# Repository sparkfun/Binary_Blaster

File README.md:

Binary Blaster Kit
==============

[Binary Blaster (KIT-12037)](https://www.sparkfun.com/products/12037)

This beginner's thru-hole soldering kit is a fun way to learn binary conversion. It displays a decimal value, 
and you are challenged to press the buttons to represent the correct binary version. Correctly press all 15 
values and you win!

Repository Contents
-------------------

* **/Firmware** - Firmware that comes programmed on the kit.
* **/Hardware** - All Eagle design files (.brd, .sch)

Documentation
-------------------
* [Assembly Guide](https://learn.sparkfun.com/tutorials/binary-blaster-assembly-guide)

License Information
-------------------
The hardware is released under [Creative Commons ShareAlike 4.0 International](https://creativecommons.org/licenses/by-sa/4.0/).
The code is beerware; if you see me (or any other SparkFun employee) at the local, and you've found our code helpful, please buy us a round!

Distributed as-is; no warranty is given.

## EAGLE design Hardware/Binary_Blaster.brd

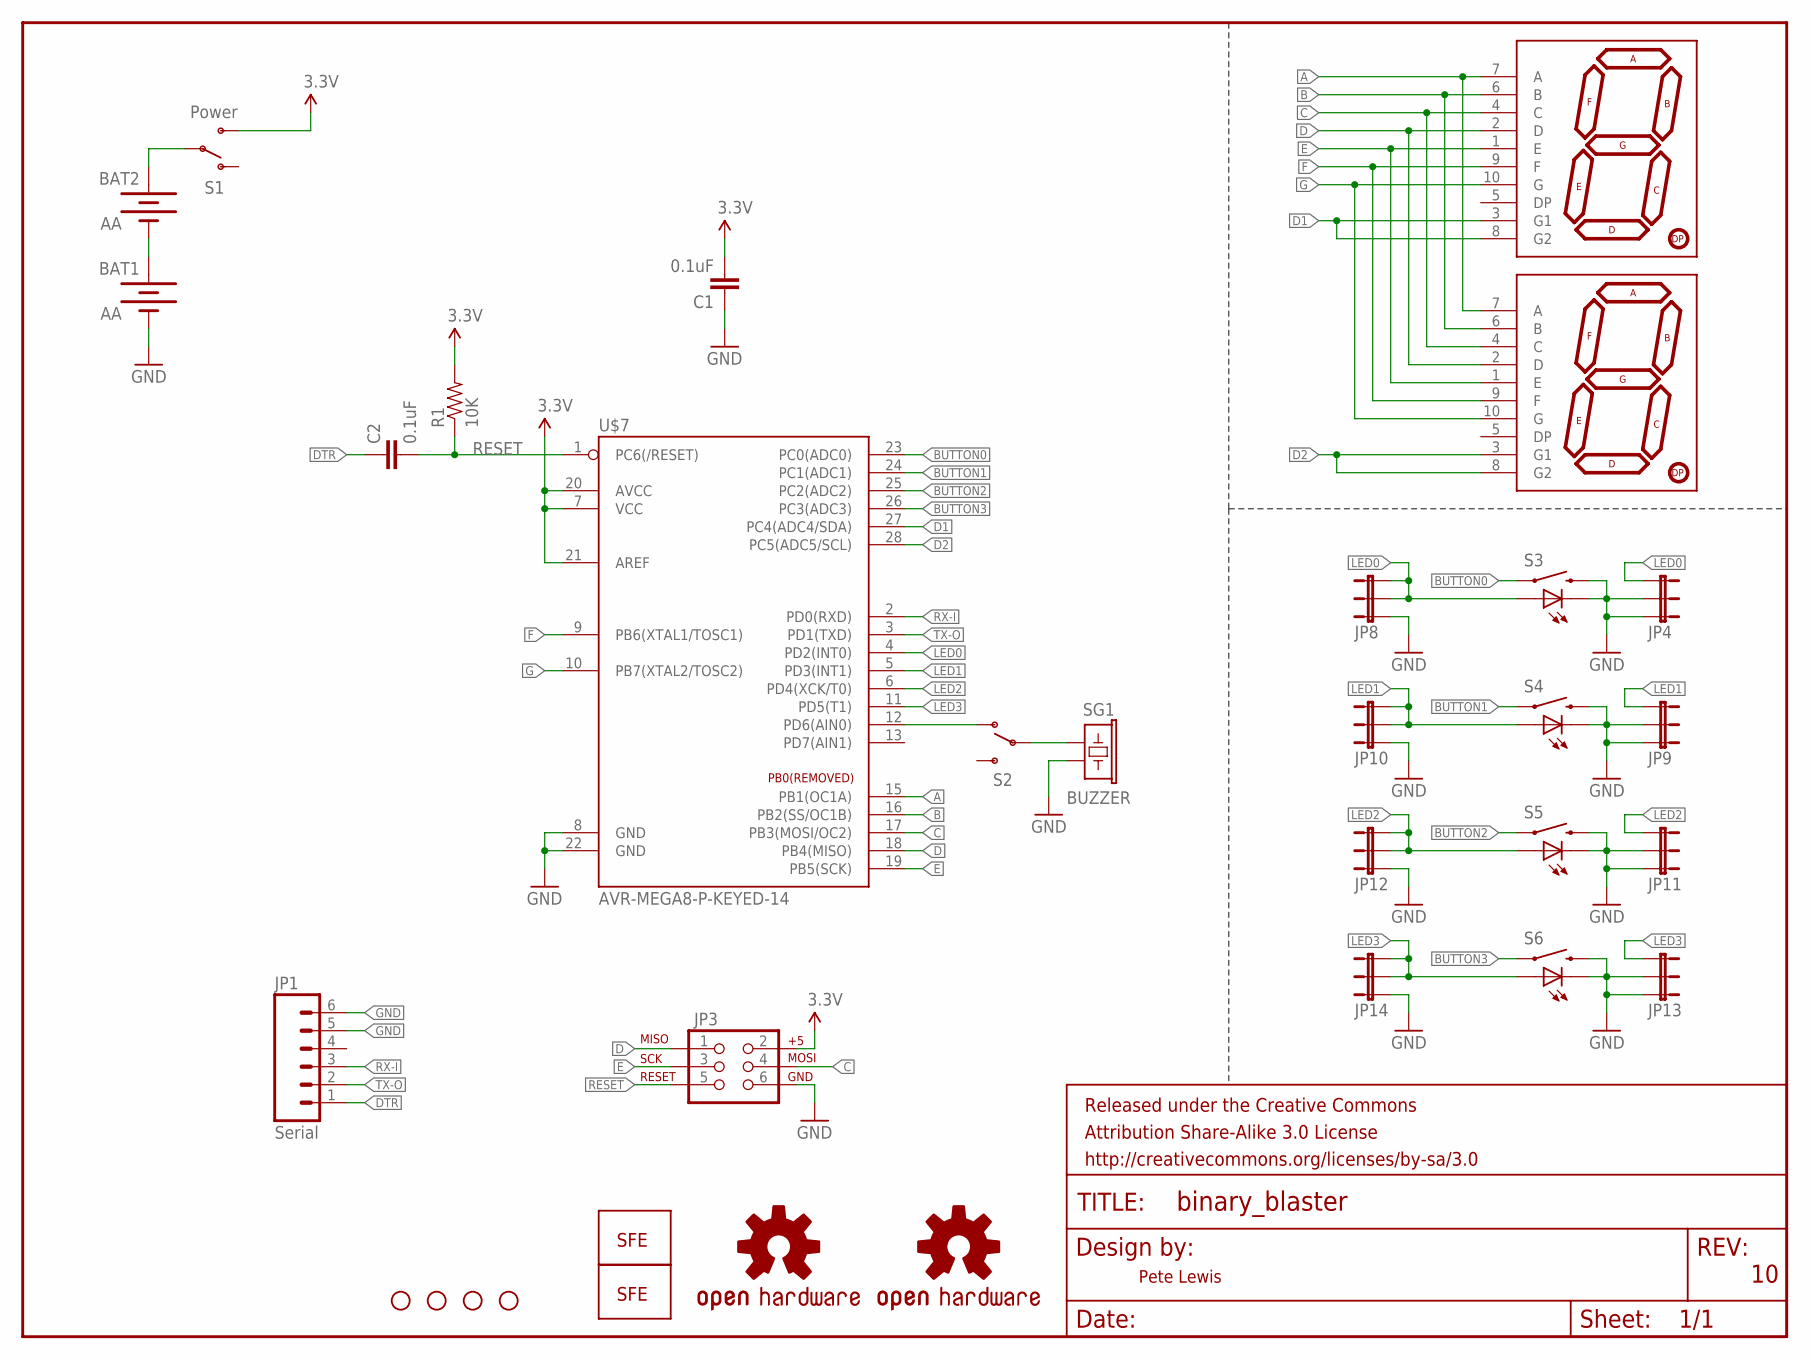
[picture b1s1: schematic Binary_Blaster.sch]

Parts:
BAT1, BAT2: AA; BATTERY-AA-KIT
C1, C2: 0.1uF; CAP-PTH-SMALL-KIT
FRAME1: FRAME-LETTER; CREATIVE_COMMONS
JP1: Serial; 1X06-NOSILK
JP2, JP5, JP6, JP7: STAND-OFF
JP3: AVR_SPI_PRG_6NS; 2X3-NS
JP4, JP8, JP9, JP10, JP11, JP12, JP13, JP14: JUMPER-3SMD; SJ_3
LOGO1, LOGO2: LOGO-SFENEW; SFE-NEW-WEBLOGO
R1: 10K; AXIAL-0.3-KIT
S1: Power; SWITCH-SPDT_KIT
S2: SWITCH-SPDTKIT; SWITCH-SPDT_KIT
S3, S4, S5, S6: SWITCH-MOMENTARY-LEDEZ; TACTILE-PTH-LED-12MM-EZ
SG1: BUZZER; BUZZER-12MM-KIT
U$1, U$6: 7-SEGMENT-DISPLAY-1"-REDEZ; 7-SEGMENT-1"PTH-EZ
U$2: OSHW-LOGOL; OSHW-LOGO-L
U$3: OSHW-LOGOS; OSHW-LOGO-S
U$7: AVR-MEGA8-P-KEYED-14; DIL28-3_KEYED-14

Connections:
3.3V: C1.2, JP3.2, R1.P$2 (2), S1.3 (S), U$7.7 (VCC), U$7.20 (AVCC), U$7.21 (AREF)
A: U$1.7 (A), U$6.7 (A), U$7.15 (PB1(OC1A))
B: U$1.6 (B), U$6.6 (B), U$7.16 (PB2(SS/OC1B))
BUTTON0: S3.4 (1), U$7.23 (PC0(ADC0))
BUTTON1: S4.4 (1), U$7.24 (PC1(ADC1))
BUTTON2: S5.4 (1), U$7.25 (PC2(ADC2))
BUTTON3: S6.4 (1), U$7.26 (PC3(ADC3))
C: JP3.4, U$1.4 (C), U$6.4 (C), U$7.17 (PB3(MOSI/OC2))
D: JP3.1, U$1.2 (D), U$6.2 (D), U$7.18 (PB4(MISO))
D1: U$1.3 (G1), U$1.8 (G2), U$7.27 (PC4(ADC4/SDA))
D2: U$6.3 (G1), U$6.8 (G2), U$7.28 (PC5(ADC5/SCL))
DTR: C2.1, JP1.1
E: JP3.3, U$1.1 (E), U$6.1 (E), U$7.19 (PB5(SCK))
F: U$1.9 (F), U$6.9 (F), U$7.9 (PB6(XTAL1/TOSC1))
G: U$1.10 (G), U$6.10 (G), U$7.10 (PB7(XTAL2/TOSC2))
GND: BAT1.GND@1 (-), C1.1, JP1.5, JP1.6, JP3.6, JP4.2, JP4.3, JP8.1, JP9.2, JP9.3, JP10.1, JP11.2, JP11.3, JP12.1, JP13.2, JP13.3, JP14.1, S3.2, S3.C, S4.2, S4.C, S5.2, S5.C, S6.2, S6.C, SG1.- (2), U$7.8 (GND), U$7.22 (GND)
LED0: JP4.1, JP8.2, JP8.3, S3.A, U$7.4 (PD2(INT0))
LED1: JP9.1, JP10.2, JP10.3, S4.A, U$7.5 (PD3(INT1))
LED2: JP11.1, JP12.2, JP12.3, S5.A, U$7.6 (PD4(XCK/T0))
LED3: JP13.1, JP14.2, JP14.3, S6.A, U$7.11 (PD5(T1))
unnamed: S2.2, SG1.+ (1)
unnamed: BAT2.PWR@1 (+), S1.2
unnamed: S2.1 (O), U$7.12 (PD6(AIN0))
unnamed: BAT1.PWR@1 (+), BAT2.GND@1 (-)
RESET: C2.2, JP3.5, R1.P$1 (1), U$7.1 (PC6(/RESET))
RX-I: JP1.3, U$7.2 (PD0(RXD))
TX-O: JP1.2, U$7.3 (PD1(TXD))

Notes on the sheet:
Pete Lewis

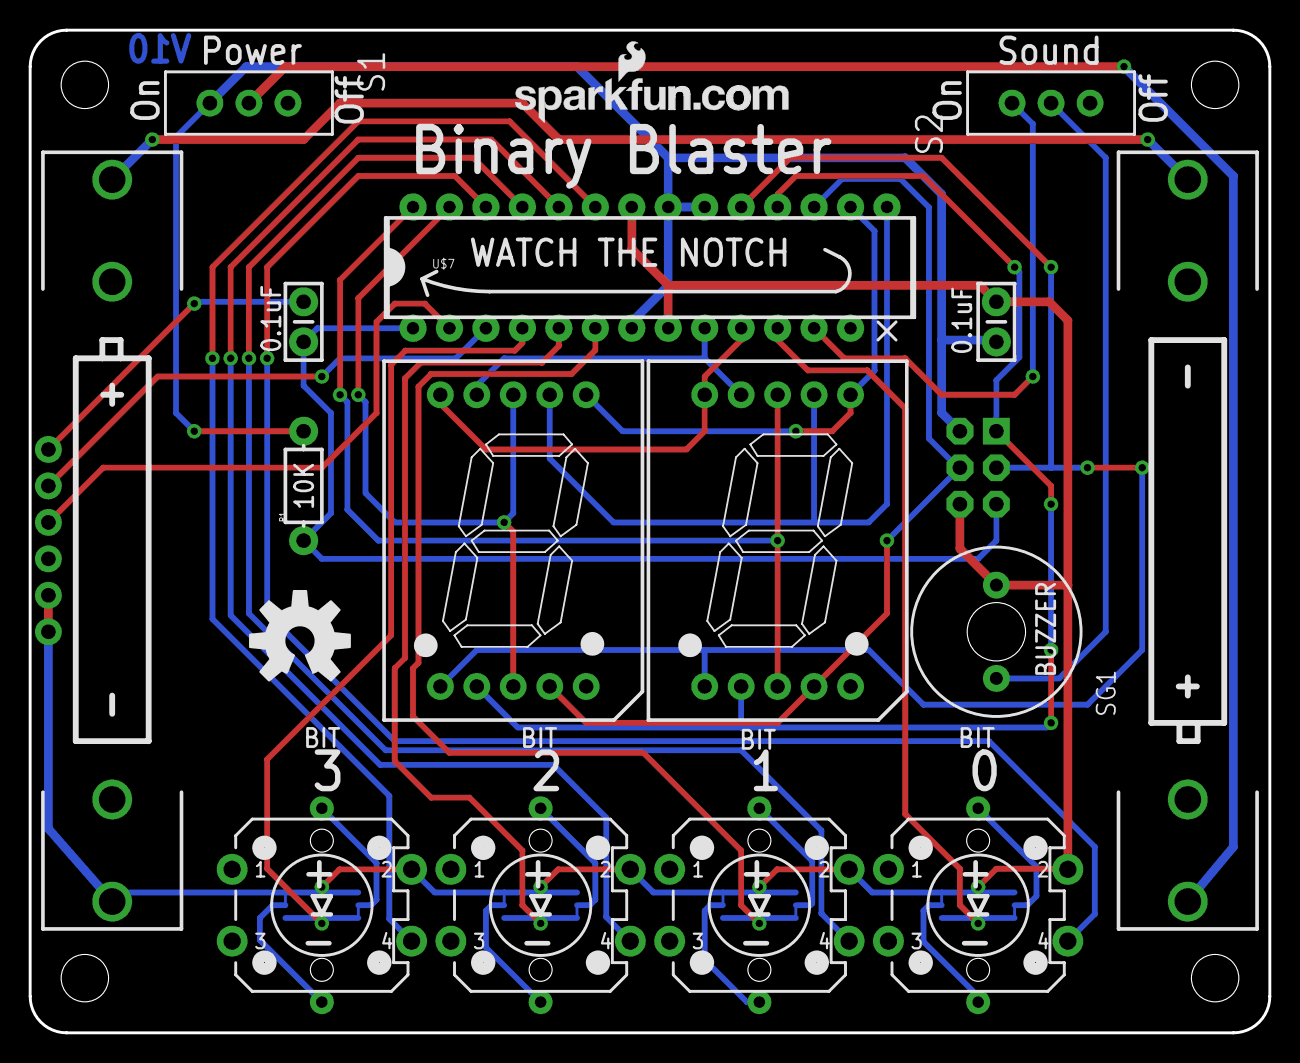
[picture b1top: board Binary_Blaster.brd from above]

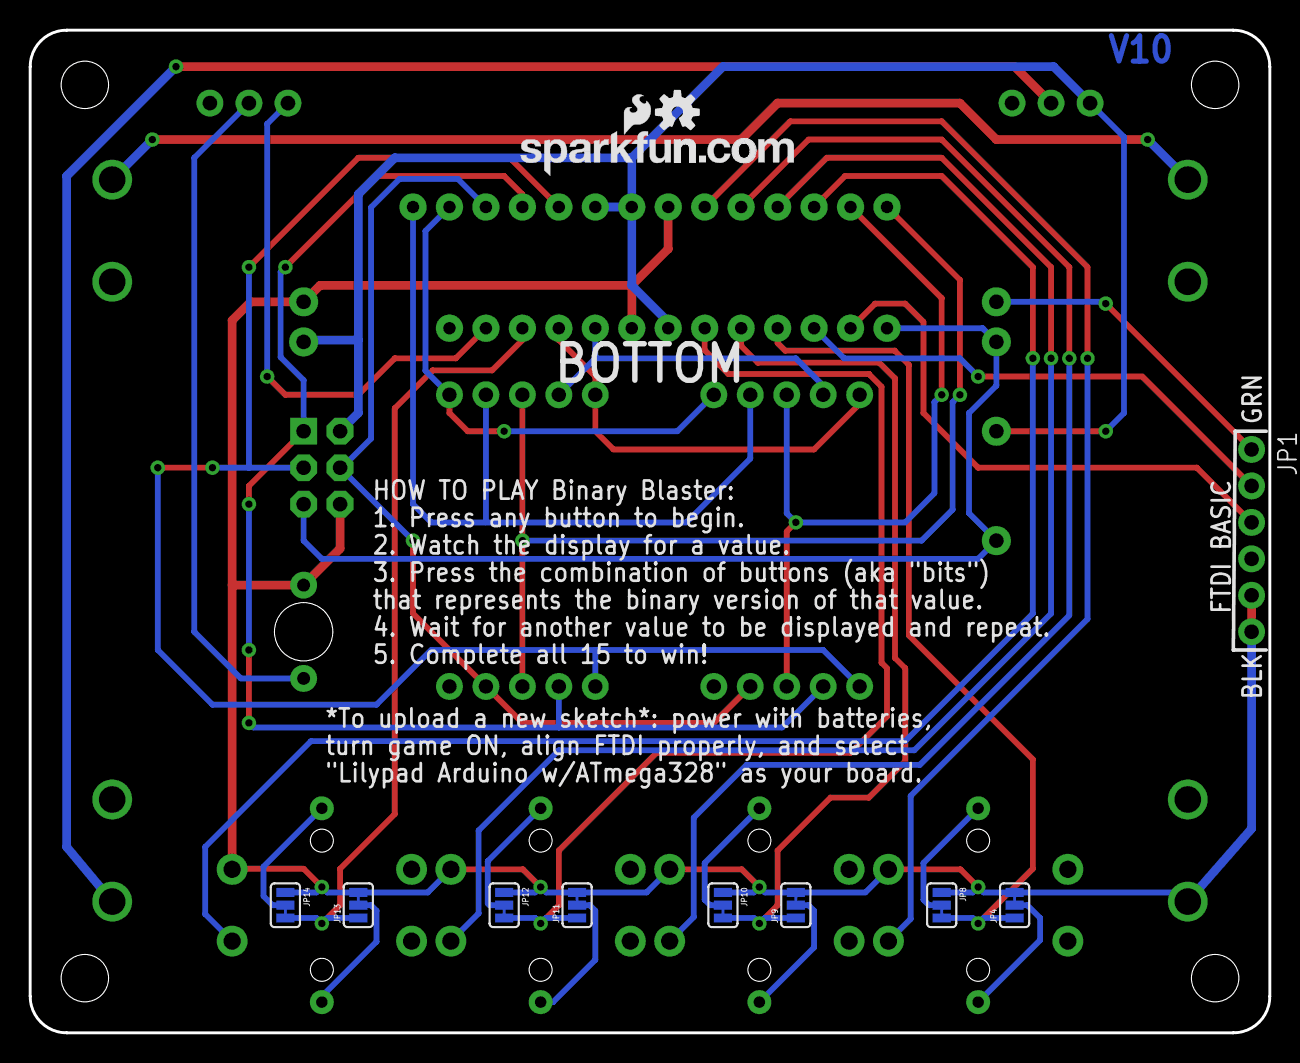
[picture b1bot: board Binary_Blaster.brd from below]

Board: 2 copper layers, 86.4 x 69.8 mm, 34 parts (12 on the bottom side), 27 nets.

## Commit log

2013-08-19 initial eagle files
2013-08-20 replaced devices with Prod_ID versions
    Also included gitignore and removed version number from board/sch file
    names.
2013-10-10 Firmware and "v02" of hardware
    v02: changed to "EZ" packages on display and leds, corrected silk on led
    package. Moved to larger display (the we carry in house).
2013-10-24 ignoring gerbers, drill files, and zipped gerbers
2013-10-24 hardware v03
    Fixed bottom silk so it no longer overlaps with pads. Also added 4 tips
    for uploading a sketch.
2013-10-29 Fixed display function for numbers above 15
    The display function was not separating the 1st and 2nd digit properly
    for displaying on the 7 segments. It was always displaying "22", "33",
    "44", or "55". Now it can show you your score properly. Also added new
    variable for total score kept in "total_time_microseconds". It will
    display this more precise score on serial debug at 9600.
2013-10-30 Added batch file fore file cleanup
    Deletes board and schematic backup files, and most common files created
    during CAM job. Also deletes zip files (where usually put cammed up
    gerbers)
2013-10-30 Updated 7-segment display to include more silk
2013-10-30 cleaned up part values on buttons
2013-10-30 Added LED polarity swap trick
    Still V03
2013-12-06 created display_roundabout_waiting()
    This helped improve response time to a button press while in waiting
    mode. It now checks for a button press after each segment lights up in
    the roundabout.
2014-01-06 V10
    -changed bottom copper version to "v10"
    -added "pete lewis" to designed by on board tname layer
    -changed version to "10" on schematic
2014-02-17 Code commenting and cleanup
    Ready for review
2014-02-17 Spell check fixes
2014-02-20 Added display_correct_conversion()
    Used when a player times out, to help teach them what they should have
    pressed.
2014-02-21 added display_counting_waiting() and changed LED reaction during gameplay
    Now the waiting mode is showing the correct values and button combos
    from 1-5. You can still hit a button to start a new game at any time.
    Also, made it so the LEDs react to your pressing during the timeout
    while loop. This is in an effort to show the player that they must hold
    down the combo of buttons at the same time. It kind of shows that the
    buttons don't change permanently because they only stay lit when you
2014-02-24 comment cleanup
2014-03-13 Updating readme with product links
2014-04-01 Added randomSeed to setup, and COMBINED hex file
    A customer, menehune23, commented on the product page about how the
    first time you play after a power cycle the order of the sequence is
    always the same. Adding a randomSeed in the setup (usuing A0 - before it
    is setup with it's internal pullup) solved the issue. Now it is much
    more random, and I doubt it will ever start with the same exact
    sequence.
2023-08-01 adjusted some settings to make it easier
    This was useful in teaching my kiddo

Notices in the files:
parts and their libraries:
SparkFun-Displays: Licensing: CC v3.0 Share-Alike You are welcome to use this library for commercial purposes.
SparkFun-Aesthetics: Released under the Creative Commons Attribution Share-Alike 3.0 License
SparkFun-Aesthetics: http://creativecommons.org/licenses/by-sa/3.0
